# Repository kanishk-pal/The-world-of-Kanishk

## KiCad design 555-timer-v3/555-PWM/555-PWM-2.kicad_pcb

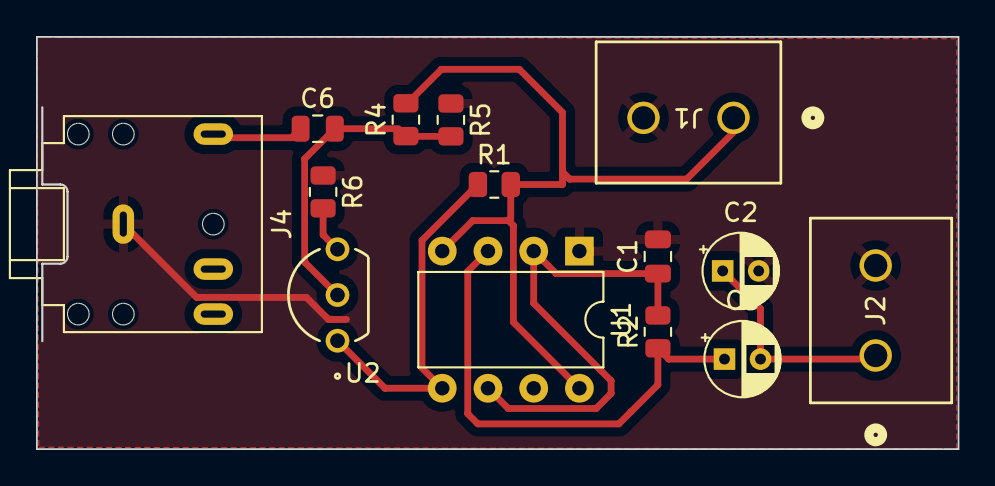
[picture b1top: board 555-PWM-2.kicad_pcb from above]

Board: 2 copper layers, 51.2 x 22.9 mm, 14 parts (0 on the bottom side), 9 nets.

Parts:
C1: 1nF; C_0805_2012Metric
C2, C3: C_Polarized_US; CP_Radial_D4.0mm_P2.00mm
C6: 100nF; C_0805_2012Metric
J1, J2: Screw_Terminal_01x02; 691137710002
J4: AudioJack3_Ground; Jack_3.5mm_CUI_SJ1-3524N_Horizontal
R1, R2: 10K; R_0805_2012Metric
R4: 100K; R_0805_2012Metric
R5: 15K; R_0805_2012Metric
R6: 1K; R_0805_2012Metric
U1: NE555D; DIP-8_W7.62mm
U2: BC547

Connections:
+9V: J1.1, R1.2, R4.2, U1.4 (R), U1.8 (VCC)
/C_timing: C1.1, R2.2, U1.2 (TR), U1.6 (THR)
/base: C6.2, R4.1, R5.2, U2.2 (BASE)
/collector: R1.1, U1.5 (CV), U2.1 (COLLECTOR)
/emitter: R6.2, U2.3 (EMITTER)
GND: C1.2, C2.2, J1.2, J2.2, J4.S, R5.1, R6.1, U1.1 (GND)
unnamed: C6.1, J4.R
unnamed: C2.1, C3.2, J2.1
unnamed: C3.1, R2.1, U1.3 (Q)

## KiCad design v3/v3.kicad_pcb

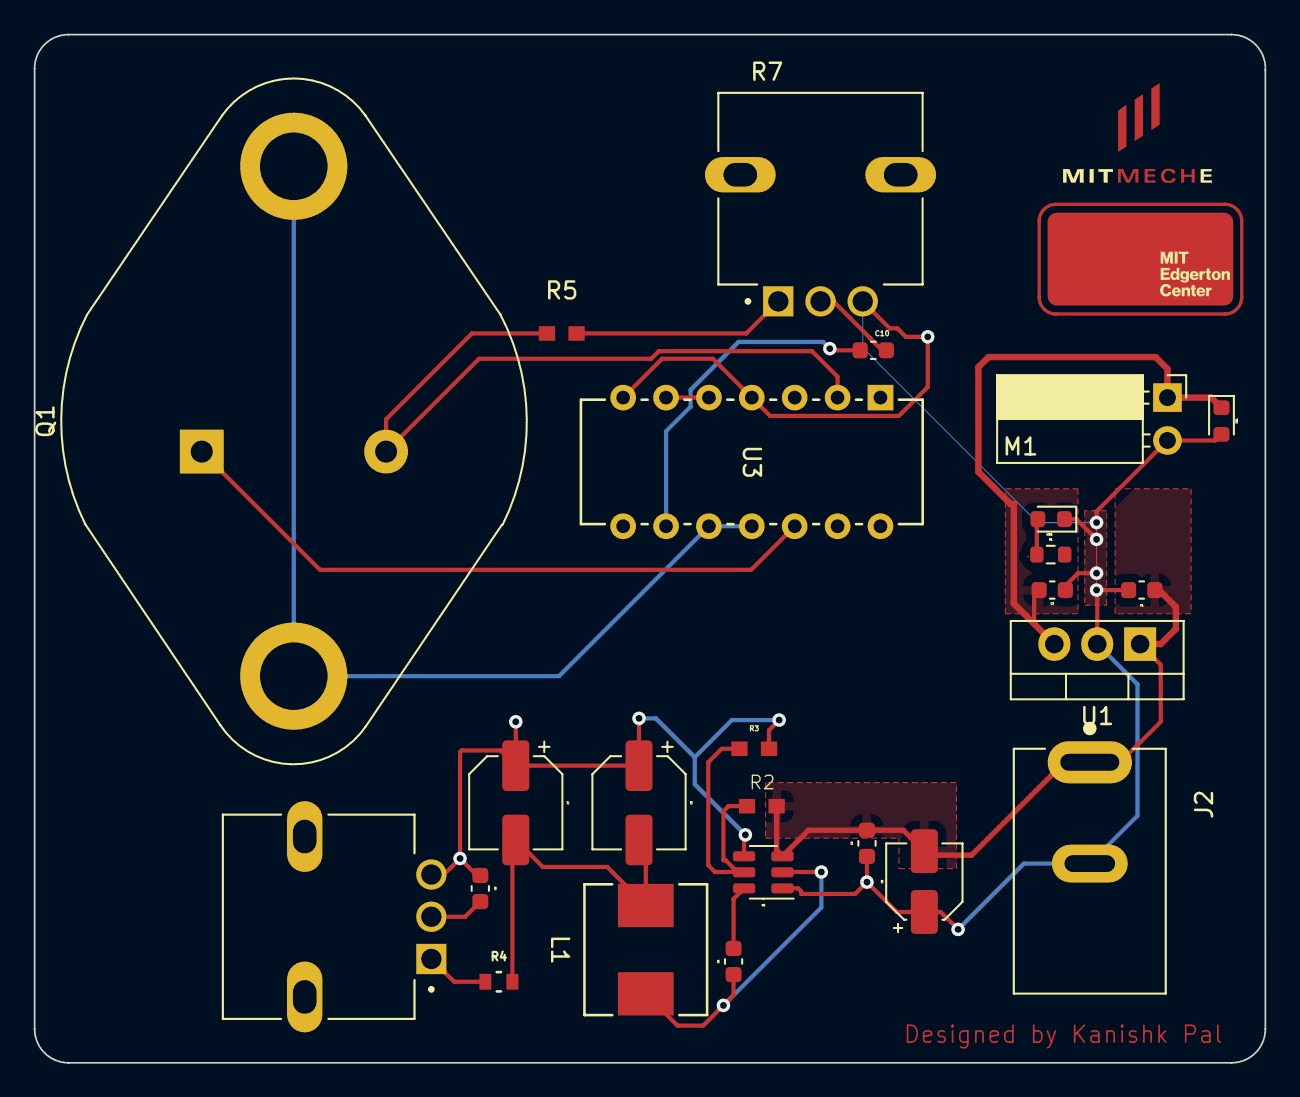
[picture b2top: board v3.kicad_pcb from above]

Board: 2 copper layers, 72.9 x 60.9 mm, 24 parts (0 on the bottom side), 14 nets.

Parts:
C1, C3: 1uF35VX5R; C_0603_1608Metric
C2: EEE-1VA100WR; CP_Elec_4x5.4
C4, C5: 0.1uF35VX5R; C_0603_1608Metric
C6, C7: UZG1V220MCL1GB; CP_Elec_5x5.3
C8: 75pF50VC0G; C_0603_1608Metric
C10: 500pF50VX7R; C_0603_1608Metric
CR1: SS34-E3/57T; D_0603_1608Metric
J2: PJ-037A; CUI_PJ-037A
L1: 10uH; IND_AMRU00060630100MA1_CHE
LED1: 5988A10107F; LED_0603_1608Metric
M1: Fan (MF40101V1-1000U-A99); PinSocket_1x02_P2.54mm_Horizontal
Q1: 2N3055; TO-3
R1: RN73R2ATTD2081A10; R_0603_1608Metric
R2: 511K; RC0603N_YAG
R3: 105K; RC0603N_YAG
R4: 49.9R; RES_RC0603_YAG
R5: 10R; RC0603N_YAG
R7: P0915N-FC15BR100K; TRIM_P0915N-FC15BR100K
U1: LM7812_TO220; TO-220-3_Vertical
U2: TPS54302; SOT-23-6
U3: LM723CN; DIP-14_STM

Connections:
+12V: C3.2, CR1.1, M1.1 (+), U1.3 (VO)
+24V: C1.1, C2.2, C4.2, J2.1, R2.1, U1.1 (VI), U2.3 (VIN)
/+V: Q1.3 (C), U3.10 (+V), U3.11 (VCC)
/I_Lim: Q1.2 (E), R5.1, U3.2 (ILIM)
/I_sen: R5.2, R7.1, U3.3 (ISEN)
/Lin_reg_out: C6.2, C7.2, L1.1, R4.2
/NInverting: U3.5 (IN+), U3.6 (VREF)
/SW: C5.1, L1.2, U2.2 (SW)
/V_out: Q1.1 (B), U3.12 (VO)
/comp: C10.1, U3.9 (FCOMP)
GND: C1.2, C2.1, C3.1, C4.1, C6.1, C7.1, C8.1, CR1.2, J2.2, LED1.1, M1.2 (-), R3.2, R7.3, U1.2 (GND), U2.1 (GND), U2.4 (FB), U3.4 (IN-), U3.7 (-V)
unnamed: C10.2, R7.2
unnamed: C5.2, U2.6 (BOOT)
unnamed: R2.2, R3.1, U2.5 (EN)

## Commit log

2024-01-17 Schematic files
2024-01-19 layout update
2024-01-20 v3_latest
2024-01-26 555-Timer
2024-01-26 555-v2
    555-v2
2024-02-01 555-timer-v3
